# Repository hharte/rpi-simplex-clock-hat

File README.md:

# RPi Simplex Clock Controller Hat

# Introduction

This project is a Raspberry Pi-compatible hat for controlling Simplex Synchronous clocks with a 24VAC motor and 24VAC correction solenoid.  This hardware can be used with the <code>[master-clock](https://github.com/hharte/master-clock.git)</code> software to implement a synchronous clock controller.

# Connectors

## Terminal block J1

<table>
  <tr>
   <td><strong><em>Pin</em></strong>
   </td>
   <td><strong><em>Name</em></strong>
   </td>
   <td><strong><em>Purpose</em></strong>
   </td>
  </tr>
  <tr>
   <td>1
   </td>
   <td>24VAC
   </td>
   <td>24VAC 60Hz Input
   </td>
  </tr>
  <tr>
   <td>2
   </td>
   <td>24VAC COM
   </td>
   <td>24VAC Common (Return)
   </td>
  </tr>
  <tr>
   <td>3
   </td>
   <td>SYNC
   </td>
   <td>24VAC Clock Sync Pulse Output
   </td>
  </tr>
  <tr>
   <td>4
   </td>
   <td>RUN
   </td>
   <td>24VAC Clock Motor control (optional)
   </td>
  </tr>
</table>

## Power Input Barrel Jacks J2, J4

Note: populate either J2 or J4.  J4 is intended to give the hat a smaller footprint when installed inside the clock housing.  J2 is intended for use with a full-size Raspberry Pi.

<table>
  <tr>
   <td><strong><em>Pin</em></strong>
   </td>
   <td><strong><em>Name</em></strong>
   </td>
   <td><strong><em>Purpose</em></strong>
   </td>
  </tr>
  <tr>
   <td>Tip
   </td>
   <td>24VAC
   </td>
   <td>24VAC 60Hz Input
   </td>
  </tr>
  <tr>
   <td>Ring
   </td>
   <td>24VAC COM
   </td>
   <td>24VAC Common (Return)
   </td>
  </tr>
</table>

Raspberry Pi J3 Signals

<table>
  <tr>
   <td><strong><em>Pin</em></strong>
   </td>
   <td><strong><em>Raspberry Pi Name</em></strong>
   </td>
   <td><strong><em>Purpose</em></strong>
   </td>
  </tr>
  <tr>
   <td>1
   </td>
   <td>3.3V DC Power
   </td>
   <td>3.3V DC Power
   </td>
  </tr>
  <tr>
   <td>2, 4
   </td>
   <td>5V DC Power
   </td>
   <td>Supplies 5VDC at 1.2A to backpower the RPi.
   </td>
  </tr>
  <tr>
   <td>11
   </td>
   <td>GPIO17
   </td>
   <td>SYNC
   </td>
  </tr>
  <tr>
   <td>13
   </td>
   <td>GPIO27
   </td>
   <td>RUN
   </td>
  </tr>
  <tr>
   <td>27
   </td>
   <td>ID_SDA
   </td>
   <td>ID EEPROM I2C Data
   </td>
  </tr>
  <tr>
   <td>28
   </td>
   <td>ID_SCL
   </td>
   <td>ID EEPROM I2C Clock
   </td>
  </tr>
</table>

# Power Supply

This board contains an AC to DC power supply to power the Raspberry Pi Zero 2 W from the same 24VAC that runs the clock motor.  If you do not wish to use this power supply to power the RPi, the following components may be omitted from your build:

<table>
  <tr>
   <td><strong><em>Reference Designator</em></strong>
   </td>
   <td><strong><em>Component</em></strong>
   </td>
  </tr>
  <tr>
   <td>D1
   </td>
   <td>Bridge rectifier
   </td>
  </tr>
  <tr>
   <td>C1, C2, C3, C4
   </td>
   <td>Capacitors
   </td>
  </tr>
  <tr>
   <td>PS1
   </td>
   <td>SPBW06-5 DC-DC Converter
   </td>
  </tr>
  <tr>
   <td>JP1
   </td>
   <td>Jumper
   </td>
  </tr>
</table>

# Jumper

When installed, JP1 provides 5VDC to the Raspberry Pi.  This hat can supply 5VDC at 1.2A, which is enough for a Raspberry Pi Zero 2W.

# Bill of Materials ([Interactive BOM](https://html-preview.github.io/?url=https://github.com/hharte/rpi-simplex-clock-hat/blob/main/hardware/bom/ibom.html))

<table>
  <tr>
   <td><strong><em>Reference</em></strong>
   </td>
   <td><strong><em>Value</em></strong>
   </td>
   <td><strong><em>Quantity</em></strong>
   </td>
   <td><strong><em><a href="https://www.digikey.com/en/mylists/list/S3O64GTQV0">DigiKey</a></em></strong>
   </td>
   <td><strong><em><a href="https://www.mouser.com/ProjectManager/ProjectDetail.aspx?AccessID=516dae8649">Mouser</a></em></strong>
   </td>
  </tr>
  <tr>
   <td>C1
   </td>
   <td>10uF / 25V
   </td>
   <td>1
   </td>
   <td><a href="https://www.digikey.com/en/products/detail/panasonic-electronic-components/ECE-A1EN100UI/2689106">ECE-A1EN100UI</a>
   </td>
   <td><a href="https://www.mouser.com/ProductDetail/Panasonic/ECE-A1EN100UI?qs=0h1gzos03f36mGOUyzNXaA%3D%3D">ECE-A1EN100UI</a>
   </td>
  </tr>
  <tr>
   <td>C2,C4,C5
   </td>
   <td>0.1uF
   </td>
   <td>3
   </td>
   <td><a href="https://www.digikey.com/en/products/detail/kemet/C315C104M5U5TA7303/3726116">C315C104M5U5TA7303</a>
   </td>
   <td><a href="https://www.mouser.com/ProductDetail/KEMET/C315C104M5U5TA7303?qs=LRwtGMyvRhhtzW9z3Tp7qQ%3D%3D">C315C104M5U5TA7303</a>
   </td>
  </tr>
  <tr>
   <td>C3
   </td>
   <td>100uF / 100V
   </td>
   <td>1
   </td>
   <td><a href="https://www.digikey.com/en/products/detail/kyocera-avx/REF1016101M100K/20096922">REF1016101M100K</a>
   </td>
   <td><a href="https://www.mouser.com/ProductDetail/KYOCERA-AVX/REF1016101M100K?qs=Y0Uzf4wQF3nLwPgf4aAj8g%3D%3D">REF1016101M100K</a>
   </td>
  </tr>
  <tr>
   <td>D1
   </td>
   <td>B250C1000G-E4/51
   </td>
   <td>1
   </td>
   <td><a href="https://www.digikey.com/en/products/detail/vishay-general-semiconductor-diodes-division/B250C1000G-E4-51/2139752">B250C1000G-E4/51</a>
   </td>
   <td><a href="https://www.mouser.com/ProductDetail/625-B250C1000G-E4">625-B250C1000G-E4</a>
   </td>
  </tr>
  <tr>
   <td>F1
   </td>
   <td>630mA
   </td>
   <td>1
   </td>
   <td><a href="https://www.digikey.com/en/products/detail/littelfuse-inc/0251-630MAT1L/700712">F7846CT-ND</a>
   </td>
   <td><a href="https://www.mouser.com/ProductDetail/Littelfuse/0251.630MAT1L?qs=LpXnx4WbYtB1cmQ95xjPnQ%3D%3D">0251.630MAT1L</a>
   </td>
  </tr>
  <tr>
   <td>J1
   </td>
   <td>TBP01R1-508-04BE
   </td>
   <td>1
   </td>
   <td><a href="https://www.digikey.com/en/products/detail/cui-devices/TBP01R1-508-04BE/10238385">TBP01R1-508-04BE</a>
   </td>
   <td><a href="https://www.mouser.com/ProductDetail/CUI-Devices/TBP01R1-508-04BE?qs=PzGy0jfpSMtbuigPwCNi2Q%3D%3D"> TBP01R1-508-04BE</a>
   </td>
  </tr>
  <tr>
   <td>P1
   </td>
   <td>TBP01P1-508-04BE
   </td>
   <td>1
   </td>
   <td><a href="https://www.digikey.com/en/products/detail/cui-devices/TBP01P1-508-04BE/10238369">TBP01P1-508-04BE</a>
   </td>
   <td><a href="https://www.mouser.com/ProductDetail/CUI-Devices/TBP01P1-508-04BE?qs=PzGy0jfpSMudTtVMrQOyVQ%3D%3D">TBP01P1-508-04BE</a>
   </td>
  </tr>
  <tr>
   <td>J2,J4
   </td>
   <td>2.1mm Barrel
   </td>
   <td>1
   </td>
   <td><a href="https://www.digikey.com/en/products/detail/switchcraft-inc/RAPC722BK/1288776">RAPC722BK</a>
   </td>
   <td><a href="https://www.mouser.com/ProductDetail/Switchcraft/RAPC722BK?qs=Nl9mtr8tY%2Fsf3BOYJcSXfg%3D%3D">RAPC722BK</a>
   </td>
  </tr>
  <tr>
   <td>J3
   </td>
   <td>2x20 female
   </td>
   <td>1
   </td>
   <td><a href="https://www.digikey.com/en/products/detail/samtec-inc/SSQ-120-01-F-D/6678748">SSQ-120-01-F-D</a>
   </td>
   <td><a href="https://www.mouser.com/ProductDetail/200-SSQ12001FD">SSQ-120-01-F-D</a>
   </td>
  </tr>
  <tr>
   <td>JP1
   </td>
   <td>Short with wire.
   </td>
   <td>-
   </td>
   <td>-
   </td>
   <td>-
   </td>
  </tr>
  <tr>
   <td>PS1
   </td>
   <td>SPBW06-05
   </td>
   <td>1
   </td>
   <td><a href="https://www.digikey.com/en/products/detail/mean-well-usa-inc/SPBW06F-05/7707011">SPBW06F-05</a>
   </td>
   <td><a href="https://www.mouser.com/ProductDetail/709-SPBW06G-05">709-SPBW06G-05</a>
   </td>
  </tr>
  <tr>
   <td>R1,R2
   </td>
   <td>220 ohm
   </td>
   <td>2
   </td>
   <td><a href="https://www.digikey.com/en/products/detail/stackpole-electronics-inc/CFM12JT220R/1741901">CFM12JT220R</a>
   </td>
   <td><a href="https://www.mouser.com/ProductDetail/YAGEO/CFR-25JR-52-220K?qs=KUIzHt%2Fe91nHT%2FPpMV7tqA%3D%3D">CFR-25JR-52-220</a>
   </td>
  </tr>
  <tr>
   <td>R3,R4
   </td>
   <td>3.9K ohm
   </td>
   <td>2
   </td>
   <td><a href="https://www.digikey.com/en/products/detail/stackpole-electronics-inc/CFM12JT3K90/1741927">S3.9KHCT-ND</a>
   </td>
   <td><a href="https://www.mouser.com/ProductDetail/YAGEO/CFR-25JR-52-3K9?qs=19cKSROHwrB%2FJo8M8ItsUQ%3D%3D">CFR-25JR-52-3K9</a>
   </td>
  </tr>
  <tr>
   <td>U1
   </td>
   <td>LAA108
   </td>
   <td>1
   </td>
   <td><a href="https://www.digikey.com/en/products/detail/ixys-integrated-circuits-division/LAA108/3077633">LAA108</a>
   </td>
   <td><a href="https://www.mouser.com/ProductDetail/IXYS-Integrated-Circuits/LAA108?qs=OpMkDkHXivMke3NLFDg0nw%3D%3D">849-LAA108</a>
   </td>
  </tr>
  <tr>
   <td>U2
   </td>
   <td>24LC256
   </td>
   <td>1
   </td>
   <td><a href="https://www.digikey.com/en/products/detail/microchip-technology/24LC64-I-P/273427">24LC64-I/P</a>
   </td>
   <td><a href="https://www.mouser.com/ProductDetail/Microchip-Technology/24LC64-I-P?qs=EkZBwCRGcSvc%252BCDluHmdqw%3D%3D">24LC64-I/P</a>
   </td>
  </tr>
  <tr>
   <td>
   </td>
   <td>8-pin DIP Sockets
   </td>
   <td>2
   </td>
   <td><a href="https://www.digikey.com/en/products/detail/assmann-wsw-components/AR-08-HZL-TT/821765">AR 08-HZL-TT</a>
   </td>
   <td><a href="https://www.mouser.com/ProductDetail/Mill-Max/110-41-308-41-001000?qs=dvxwXVM4mZVj1CY1TePuww%3D%3D">110-41-308-41-001000</a>
   </td>
  </tr>
</table>

# Hat ID EEPROM

The board contains a footprint for a 24C256 or similar serial EEPROM.  This EEPROM connects to the Raspberry Pi’s i2c-0 port, and contains configuration data describing the hat.

The i2c-0 port needs to be enabled in `/boot/config.txt` by manually adding the line:

```
dtparam=i2c_vc=on
```

And uncommenting:

```
dtparam=i2c_arm=on
```

Reboot the Pi and make sure the EEPROM is detected at address 0x50:

```
$ i2cdetect -y 0
     0  1  2  3  4  5  6  7  8  9  a  b  c  d  e  f
00:                         -- -- -- -- -- -- -- --
10: -- -- -- -- -- -- -- -- -- -- -- -- -- -- -- --
20: -- -- -- -- -- -- -- -- -- -- -- -- -- -- -- --
30: -- -- -- -- -- -- -- -- -- -- -- -- -- -- -- --
40: -- -- -- -- -- -- -- -- -- -- -- -- -- -- -- --
50: 50 -- -- -- -- -- -- -- -- -- -- -- -- -- -- --
60: -- -- -- -- -- -- -- -- -- -- -- -- -- -- -- --
70: -- -- -- -- -- -- -- --
```

Use utilities from here: [https://github.com/raspberrypi/hats](https://github.com/raspberrypi/hats)

```
$ git clone https://github.com/raspberrypi/hats
$ cd hats/eepromutils/
$ make
$ ./eepmake rpi-simplex-clock-hat.txt rpi-simplex-clock-hat.eep
$ sudo ./eepflash.sh -w -f=./rpi-simplex-clock-hat.eep -t=24c64 -d=0
This will attempt to talk to an eeprom at i2c address 0x50. Make sure there is an eeprom at this address.
This script comes with ABSOLUTELY no warranty. Continue only if you know what you are doing.
Do you wish to continue? (yes/no): yes
Writing...
0+1 records in
0+1 records out
149 bytes copied, 0.660765 s, 0.2 kB/s
Closing EEPROM Device.
Done.
```

Read EEPROM to a file:

```
sudo ./eepflash.sh -r -t=24c64 -f=readout.eep
```

After programming the EEPROM and rebooting, the hat information should be available in `/proc/device-tree/hat/`

# Mounting Brackets

3D-printable mounting brackets for the [Raspberry Pi Zero 2 W](https://github.com/hharte/rpi-simplex-clock-hat/blob/main/mounting/rpi-zero-simplex-clock-mounting.stl) and [full-size Raspberry Pi](https://github.com/hharte/rpi-simplex-clock-hat/blob/main/mounting/rpi-simplex-clock-mounting.stl) are provided.  The Raspberry Pi Zero 2 W can fit inside the clock movement housing.

# Software Installation

The software for this project consists of Raspberry Pi OS as well as a [Master Clock Daemon](https://github.com/hharte/master-clock.git) which is a Python script that activates the SYNC output at the correct times for hourly and 12-hour corrections.

## Raspberry Pi Zero 2 W

Install Raspberry Pi OS to MicroSD card using Raspberry Pi Imager.  Select Raspberry Pi OS (other) → Raspberry Pi OS (Legacy, 32-bit) Lite.

Change settings to enable WiFi with SSID/Password, set WiFi country, set locale, set username/password.

After booting the Raspberry Pi, ssh in and:

```
$ sudo apt-get install ntpdate
$ sudo ntpdate time.google.com
$ sudo apt-get update; sudo apt-get upgrade
$ sudo apt-get install git gpiod i2c-tools
$ git clone https://github.com/hharte/master-clock.git
```

### Configure Service

Edit `simplex_master_clock.service` and change the following line to the correct path for `simplex_master_clock.py`:

ExecStart=/usr/bin/python3 /home/pi/master-clock/simplex_master_clock.py

### Install Service

```
$ sudo cp simplex_master_clock.service /etc/systemd/system/
$ sudo systemctl enable simplex_master_clock.service
$ sudo systemctl start simplex_master_clock.service
$ sudo systemctl status simplex_master_clock.service
```

# Clock Connectors

The Simplex synchronous clocks typically have a 4-pin female Molex MLX connector.  These connectors, pins, and tools are available from Amazon:

Connectors: [https://www.amazon.com/dp/B07DKZQK5M](https://www.amazon.com/dp/B07DKZQK5M)

Crimper: [https://www.amazon.com/gp/product/B0C8MXNWDK](https://www.amazon.com/gp/product/B0C8MXNWDK)

Pin Extractor: DAP-T292328: [https://www.amazon.com/dp/B0C4NWRQD4](https://www.amazon.com/dp/B0C4NWRQD4)

# Clock Movement Bushings

The clock movements are mounted using pins with spring clips and rubber bushings.  These rubber bushings become dried out and brittle with age.  If you would like to replace them, the ¼” grommets in this kit work well: [300 Pcs Rubber Grommets Kit](https://www.amazon.com/gp/product/B0BXKXMT55).

# Compatibility with other Pi Hats

The synchronous clock controller is designed to support piggybacking with the [Uputronics Pi GPS/RTC Expansion Board](https://store.uputronics.com/index.php?route=product/product&product_id=81).  When used in conjunction with the GPS Expansion Board, a complete accurate time solution can be realized.

# Revision History

Rev 0 → Rev 1

1. Turn SSRs on with logic 1 to GPIO outputs.  This is needed so that the SSRs don't become enabled when the GPIO17 and GPIO27 are set to outputs during boot.  These GPIOs are pulled low on the RPi.
2. Add alternate footprint location (J4) for AC input barrel jack.
3. Add additional mounting holes for Raspberry Pi Zero / Zero 2 W.
4. Correct pinout for the bridge rectifier D1.

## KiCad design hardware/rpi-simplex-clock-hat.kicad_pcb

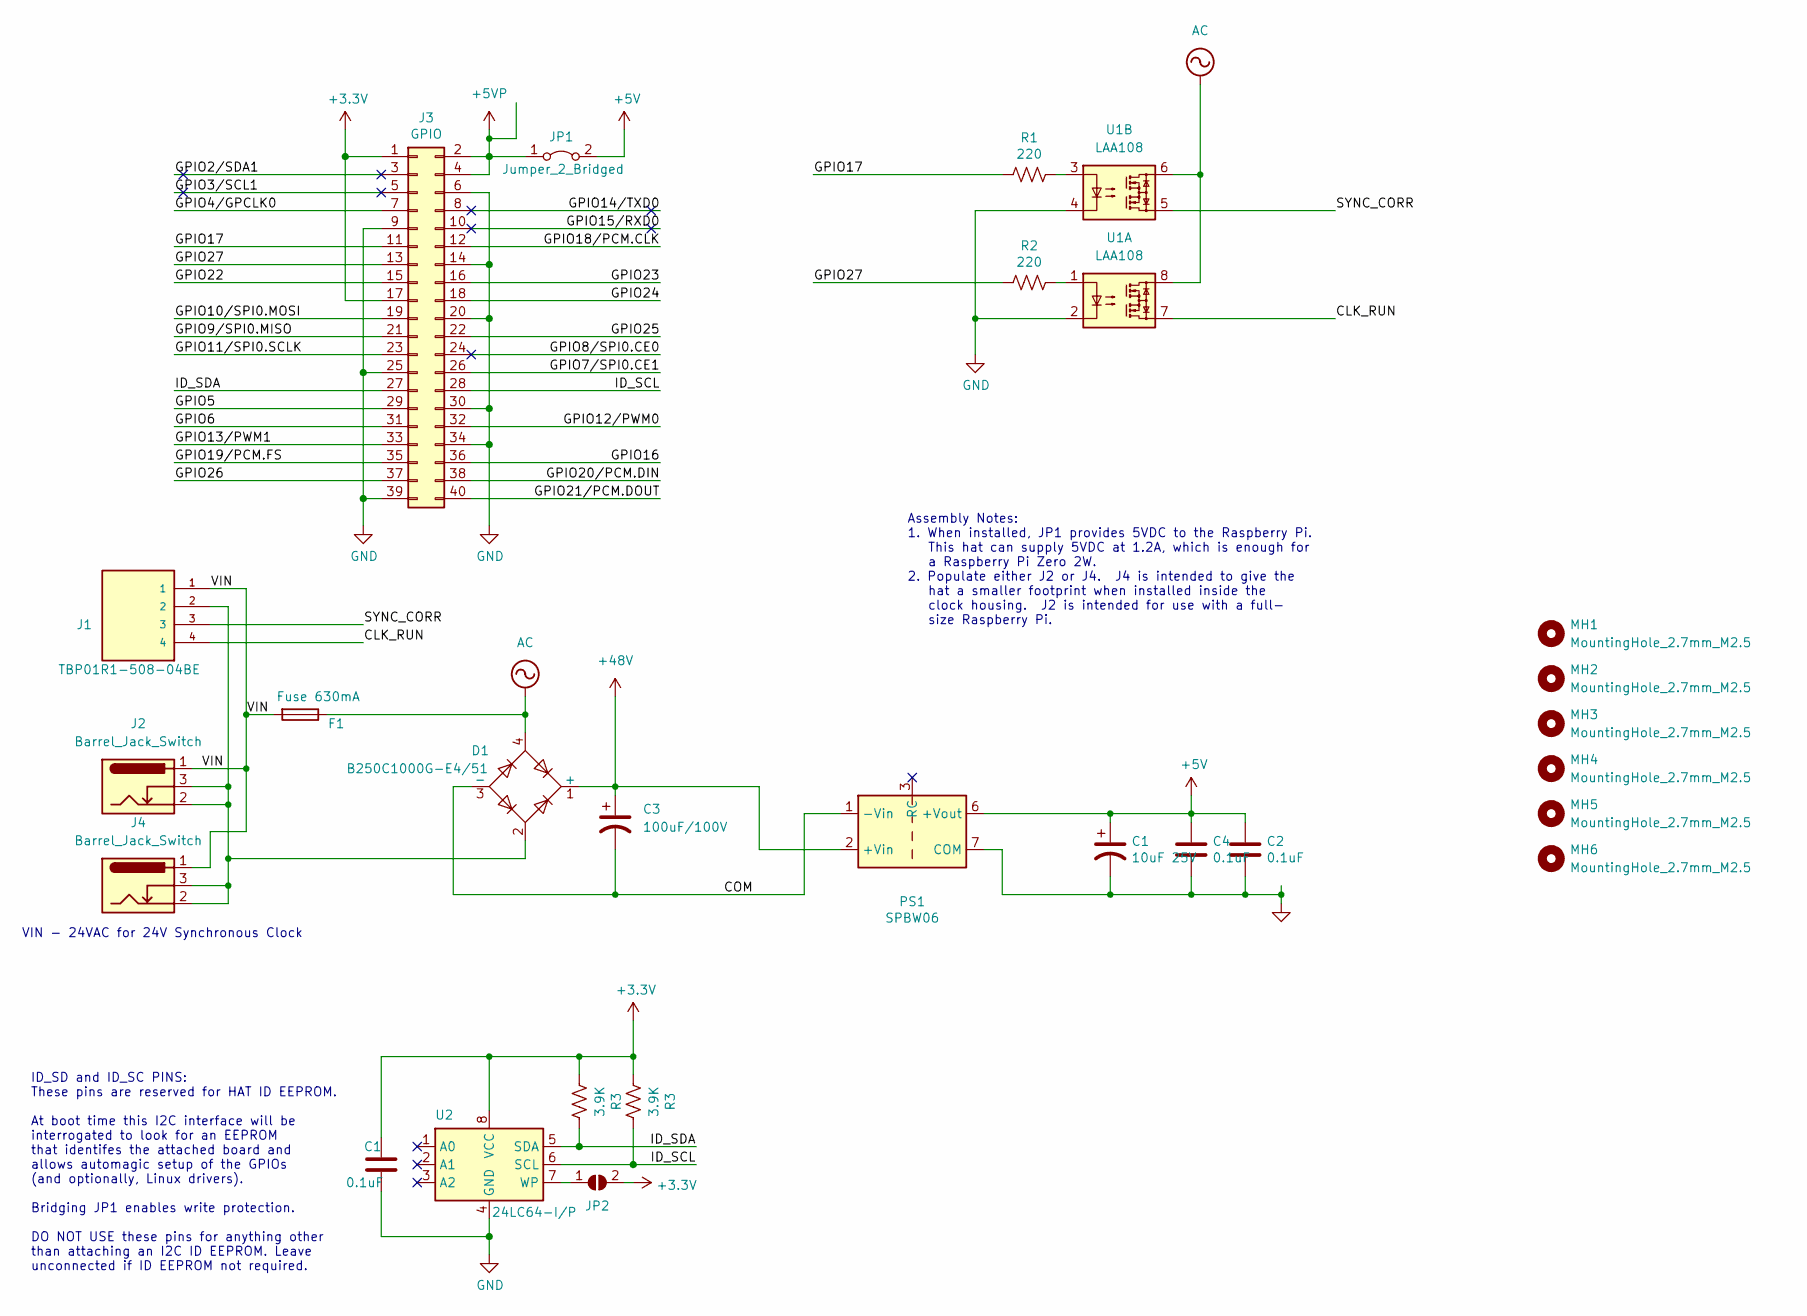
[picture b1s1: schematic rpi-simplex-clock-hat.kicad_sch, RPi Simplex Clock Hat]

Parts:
C1, C2, C4: 0.1uF; C_Disc_D3.0mm_W2.0mm_P2.50mm; MPN C315C104M5U5TA7303
C3: 100uF/100V; CP_Radial_D10.0mm_P5.00mm; MPN REF1016101M100K
D1: B250C1000G-E4/51; Diode_Bridge_Round_D9.8mm; MPN B250C1000G-E4/51
F1: Fuse 630mA; R_Axial_DIN0309_L9.0mm_D3.2mm_P12.70mm_Horizontal; MPN 0251.630MAT1L
J1: TBP01R1-508-04BE; CUI_TBP01R1-508-04BE; MPN TBP01R1-508-04BE
J2, J4: Barrel_Jack_Switch; BarrelJack_Horizontal; MPN RAPC722BK
J3: GPIO; PinSocket_2x20_P2.54mm_Vertical; MPN SSQ-120-01-F-D
JP1: Jumper_2_Bridged; PinHeader_1x02_P2.54mm_Vertical
JP2: ID_WP; SolderJumper-2_P1.3mm_Open_Pad1.0x1.5mm
MH1, MH2, MH3, MH4, MH5, MH6: MountingHole_2.7mm_M2.5
PS1: SPBW06; Converter_DCDC_TRACO_TMR-xxxx_THT; MPN SPBW06F-05
R1, R2: 220; R_Axial_DIN0207_L6.3mm_D2.5mm_P7.62mm_Horizontal; MPN CFM12JT220R
R3: 3.9K; R_Axial_DIN0207_L6.3mm_D2.5mm_P2.54mm_Vertical; MPN CFM12JT3K90
U1: LAA108; DIP-8_W7.62mm_Socket; MPN LAA108
U2: 24LC64-I/P; DIP-8_W7.62mm_Socket; MPN 24LC64-I/P

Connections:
+5VP: J3.2, J3.4, JP1.1 (A)
+48V: C3.1, D1.1 (+), PS1.2 (+Vin)
/CLK_RUN: J1.4, U1.7
/COM: C3.2, D1.3 (-), PS1.1 (-Vin)
/GPIO2/SDA1: J3.3
/GPIO3/SCL1: J3.5
/GPIO4/GPCLK0: J3.7
/GPIO5: J3.29
/GPIO6: J3.31
/GPIO7/SPI0.CE1: J3.26
/GPIO8/SPI0.CE0: J3.24
/GPIO9/SPI0.MISO: J3.21
/GPIO10/SPI0.MOSI: J3.19
/GPIO11/SPI0.SCLK: J3.23
/GPIO12/PWM0: J3.32
/GPIO13/PWM1: J3.33
/GPIO14/TXD0: J3.8
/GPIO15/RXD0: J3.10
/GPIO16: J3.36
/GPIO17: J3.11, R1.2
/GPIO18/PCM.CLK: J3.12
/GPIO19/PCM.FS: J3.35
/GPIO20/PCM.DIN: J3.38
/GPIO21/PCM.DOUT: J3.40
/GPIO22: J3.15
/GPIO23: J3.16
/GPIO24: J3.18
/GPIO25: J3.22
/GPIO26: J3.37
/GPIO27: J3.13, R2.2
/SYNC_CORR: J1.3, U1.5
/VIN: F1.2, J1.1, J2.1, J4.1
AC: D1.4, F1.1, U1.6, U1.8
GND: C1.2, C2.2, C4.2, J3.6, J3.9, J3.14, J3.20, J3.25, J3.30, J3.34, J3.39, PS1.7 (COM), U1.2, U1.4, U2.4 (GND); also elsewhere on the board
unnamed: D1.2, J1.2, J2.2, J2.3, J4.2, J4.3
unnamed: JP2.1 (A), U2.7 (WP)
unnamed: R1.1, U1.3
unnamed: R2.1, U1.1

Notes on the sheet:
VIN - 24VAC for 24V Synchronous Clock
Assembly Notes: 1. When installed, JP1 provides 5VDC to the Raspberry Pi. This hat can supply 5VDC at 1.2A, which is enough for a Raspberry Pi Zero 2W. 2. Populate either J2 or J4. J4 is intended to give the hat a smaller footprint when installed inside the clock housing. J2 is intended for use wit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
ID_SD and ID_SC PINS: These pins are reserved for HAT ID EEPROM. At boot time this I2C interface will be interrogated to look for an EEPROM that identifes the attached board and allows automagic setup of the GPIOs (and optionally, Linux drivers). Bridging JP1 enables write protection. DO NOT USE th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

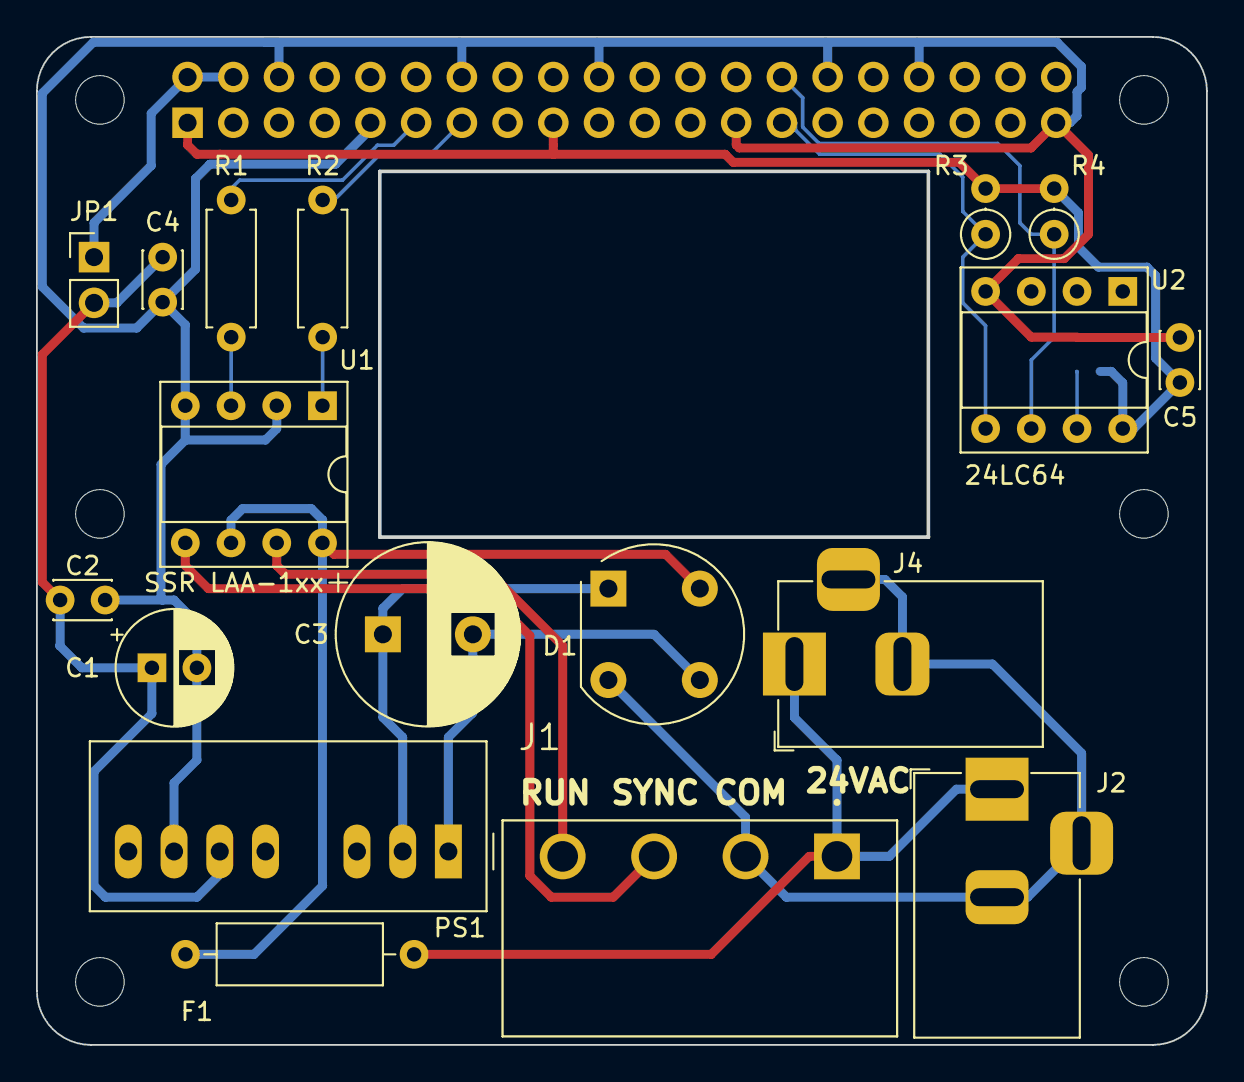
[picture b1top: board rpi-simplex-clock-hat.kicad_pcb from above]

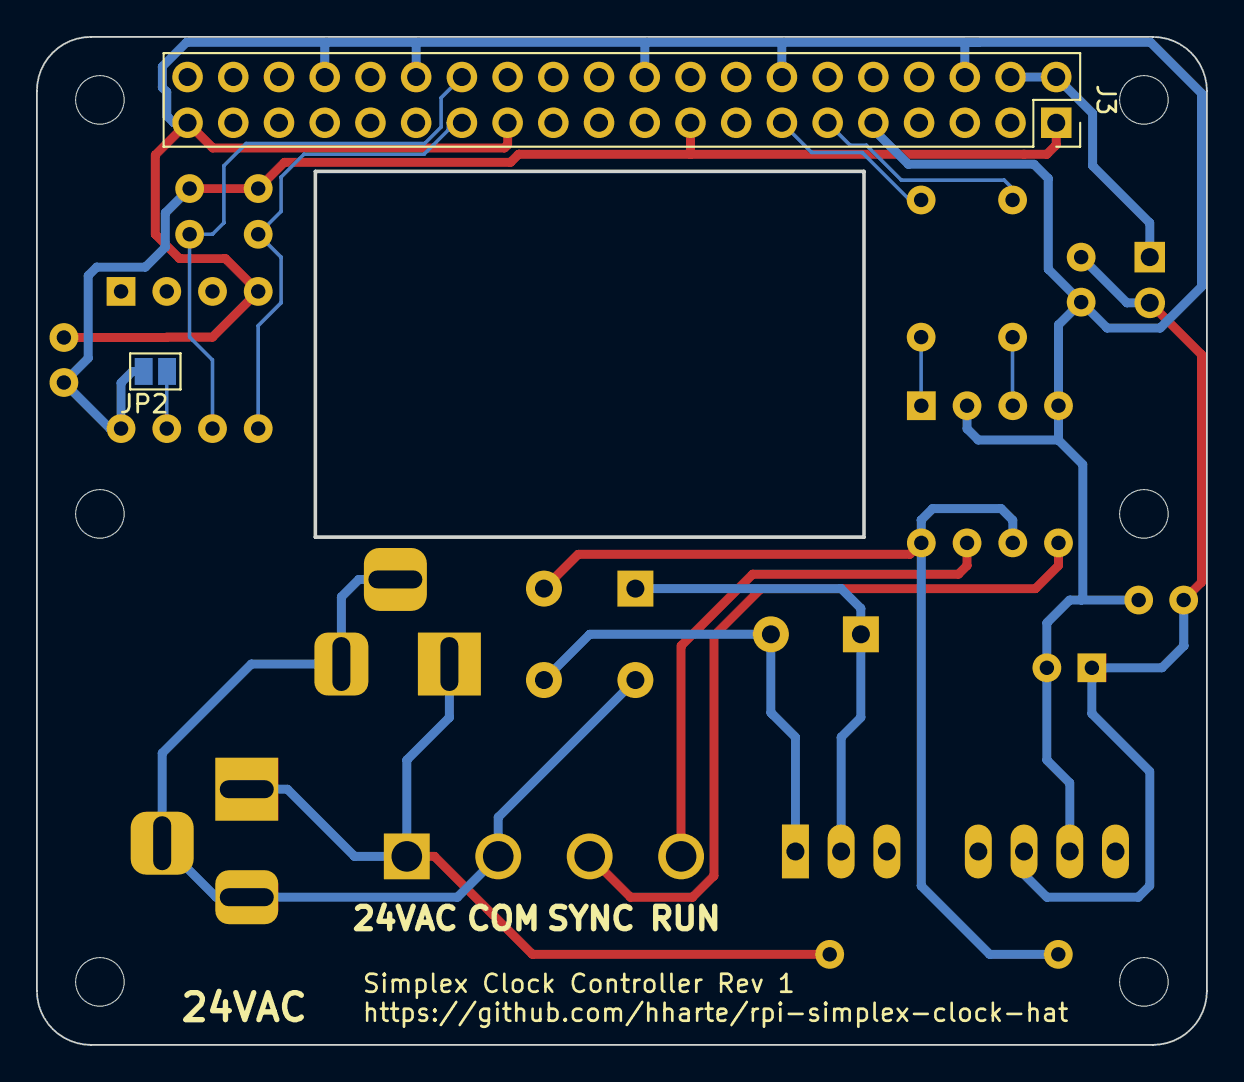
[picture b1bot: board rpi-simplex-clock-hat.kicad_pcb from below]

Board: 2 copper layers, 65.0 x 56.0 mm, 26 parts (2 on the bottom side), 18 nets.

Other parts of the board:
C5: 0.1uF; C_Disc_D3.0mm_W2.0mm_P2.50mm
R4: 3.9K; R_Axial_DIN0207_L6.3mm_D2.5mm_P2.54mm_Vertical

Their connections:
GND: C5.2; also elsewhere on the board

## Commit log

2024-02-04 Initial Rev 0 version, fabbed out 2024-02-03.
2024-02-17 Update EEPROM UUID and add .eep file
2024-02-17 Rev 1: Fix minor issues in Rev 0.
    1. Turn SSRs on with logic 1 to GPIO outputs. This is needed so that
    the SSRs don't become enabled when the GPIO17 and GPIO27 are set to
    outputs. These GPIOs are pulled low.
    2. Add alternate footprint location (J4) for AC input barrel jack.
    3. Add additional mounting holes for Raspberry Pi Zero / Zero 2 W.
    4. Correct pinout for the bridge rectifier D1.
2024-03-10 Mounting plates for RPi Zero 2W and full-size RPi.
2024-03-23 Add interactive BOM, update to KiCAD 8.0.1.
